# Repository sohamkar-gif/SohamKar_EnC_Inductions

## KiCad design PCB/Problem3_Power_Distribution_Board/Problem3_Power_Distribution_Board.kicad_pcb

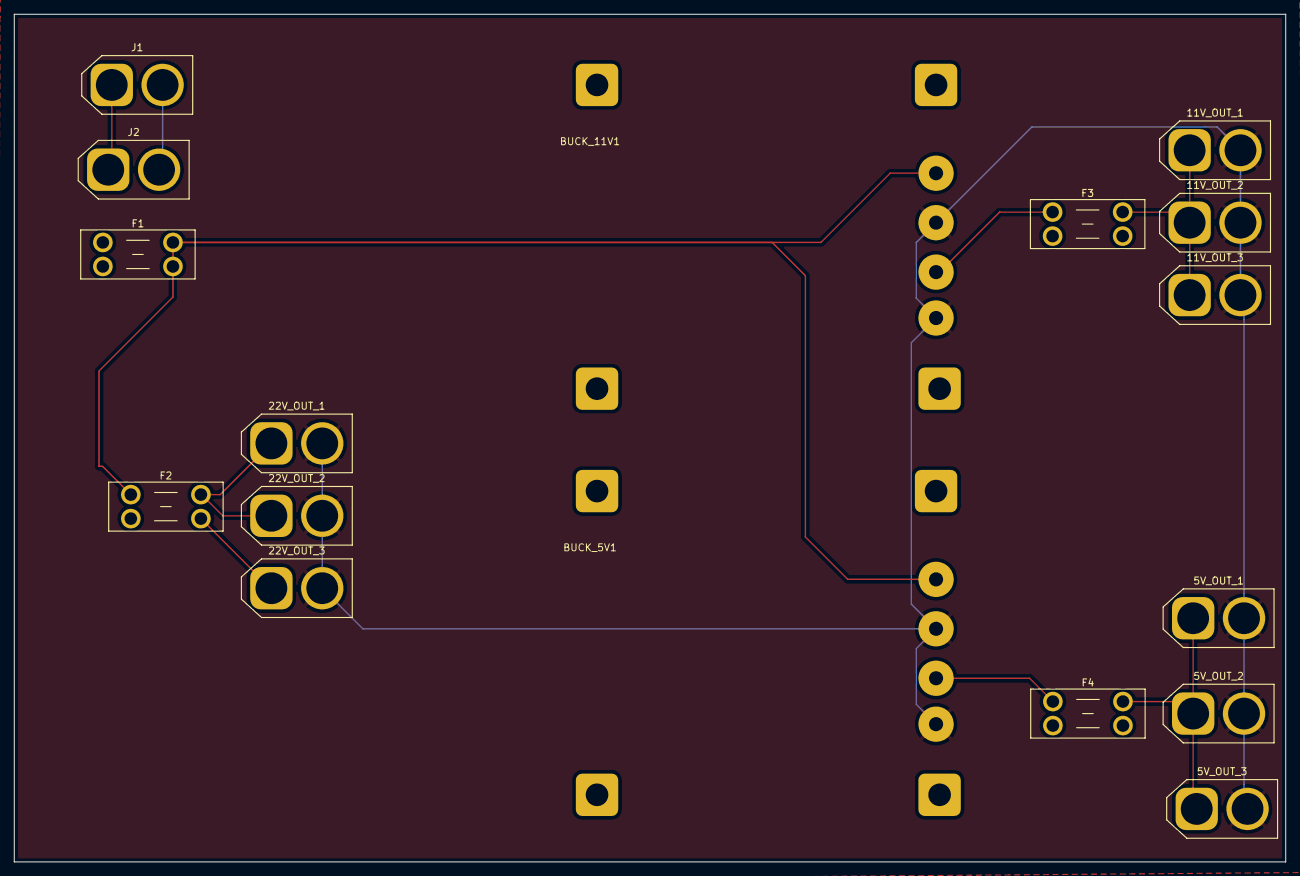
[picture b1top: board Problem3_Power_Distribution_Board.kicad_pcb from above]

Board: 2 copper layers, 180.0 x 120.0 mm, 17 parts (0 on the bottom side), 7 nets.

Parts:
5V_OUT_1, 5V_OUT_2, 5V_OUT_3, 11V_OUT_1, 11V_OUT_2, 11V_OUT_3, 22V_OUT_1, 22V_OUT_2, 22V_OUT_3: Conn_01x02; AMASS_XT60-F_1x02_P7.20mm_Vertical
BUCK_5V1, BUCK_11V1: Conn_01x04; Buck_20A_Module
F1: 30A; Fuseholder_Blade_Mini_Keystone_3568
F2: 20A; Fuseholder_Blade_Mini_Keystone_3568
F3: 15A; Fuseholder_Blade_Mini_Keystone_3568
F4: 6A; Fuseholder_Blade_Mini_Keystone_3568
J1: Battery 1; AMASS_XT60-F_1x02_P7.20mm_Vertical
J2: Batter 2; AMASS_XT60-F_1x02_P7.20mm_Vertical

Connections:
/+22V_MAIN: BUCK_5V1.VIN+ (Pin_1), BUCK_11V1.VIN+ (Pin_1), F1.2, F2.1
GND: 5V_OUT_1.2, 5V_OUT_2.2, 5V_OUT_3.2, 11V_OUT_1.2, 11V_OUT_2.2, 11V_OUT_3.2, 22V_OUT_1.2, 22V_OUT_2.2, 22V_OUT_3.2, BUCK_5V1.VIN- (Pin_2), BUCK_5V1.VOUT- (Pin_4), BUCK_11V1.VIN- (Pin_2), BUCK_11V1.VOUT- (Pin_4)
unnamed: 5V_OUT_1.1, 5V_OUT_2.1, 5V_OUT_3.1, F4.2
unnamed: 11V_OUT_1.1, 11V_OUT_2.1, 11V_OUT_3.1, F3.2
unnamed: 22V_OUT_1.1, 22V_OUT_2.1, 22V_OUT_3.1, F2.2
unnamed: BUCK_5V1.VOUT+ (Pin_3), F4.1
unnamed: BUCK_11V1.VOUT+ (Pin_3), F3.1
